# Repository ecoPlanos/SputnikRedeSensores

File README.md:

# SputnikRedeSensores

Open source project of a sensors test suit.

The goal is to develop a system to compare several sensors of each type out of several types.
The sensors will be assembled on a PCB for each type, that will connect to an Arduino Due compatible shield.
A program running on the Arduino, will log sensors data to a SD card and make it accessible through a FTP server.

types of sensors:
Temperature and relative humidity;
Superficial temperature;
Motion detection;
Air quality;
Electrical current;
Water flow;
Proximity;
Distance;
Microwave;
Lumen;
UV.

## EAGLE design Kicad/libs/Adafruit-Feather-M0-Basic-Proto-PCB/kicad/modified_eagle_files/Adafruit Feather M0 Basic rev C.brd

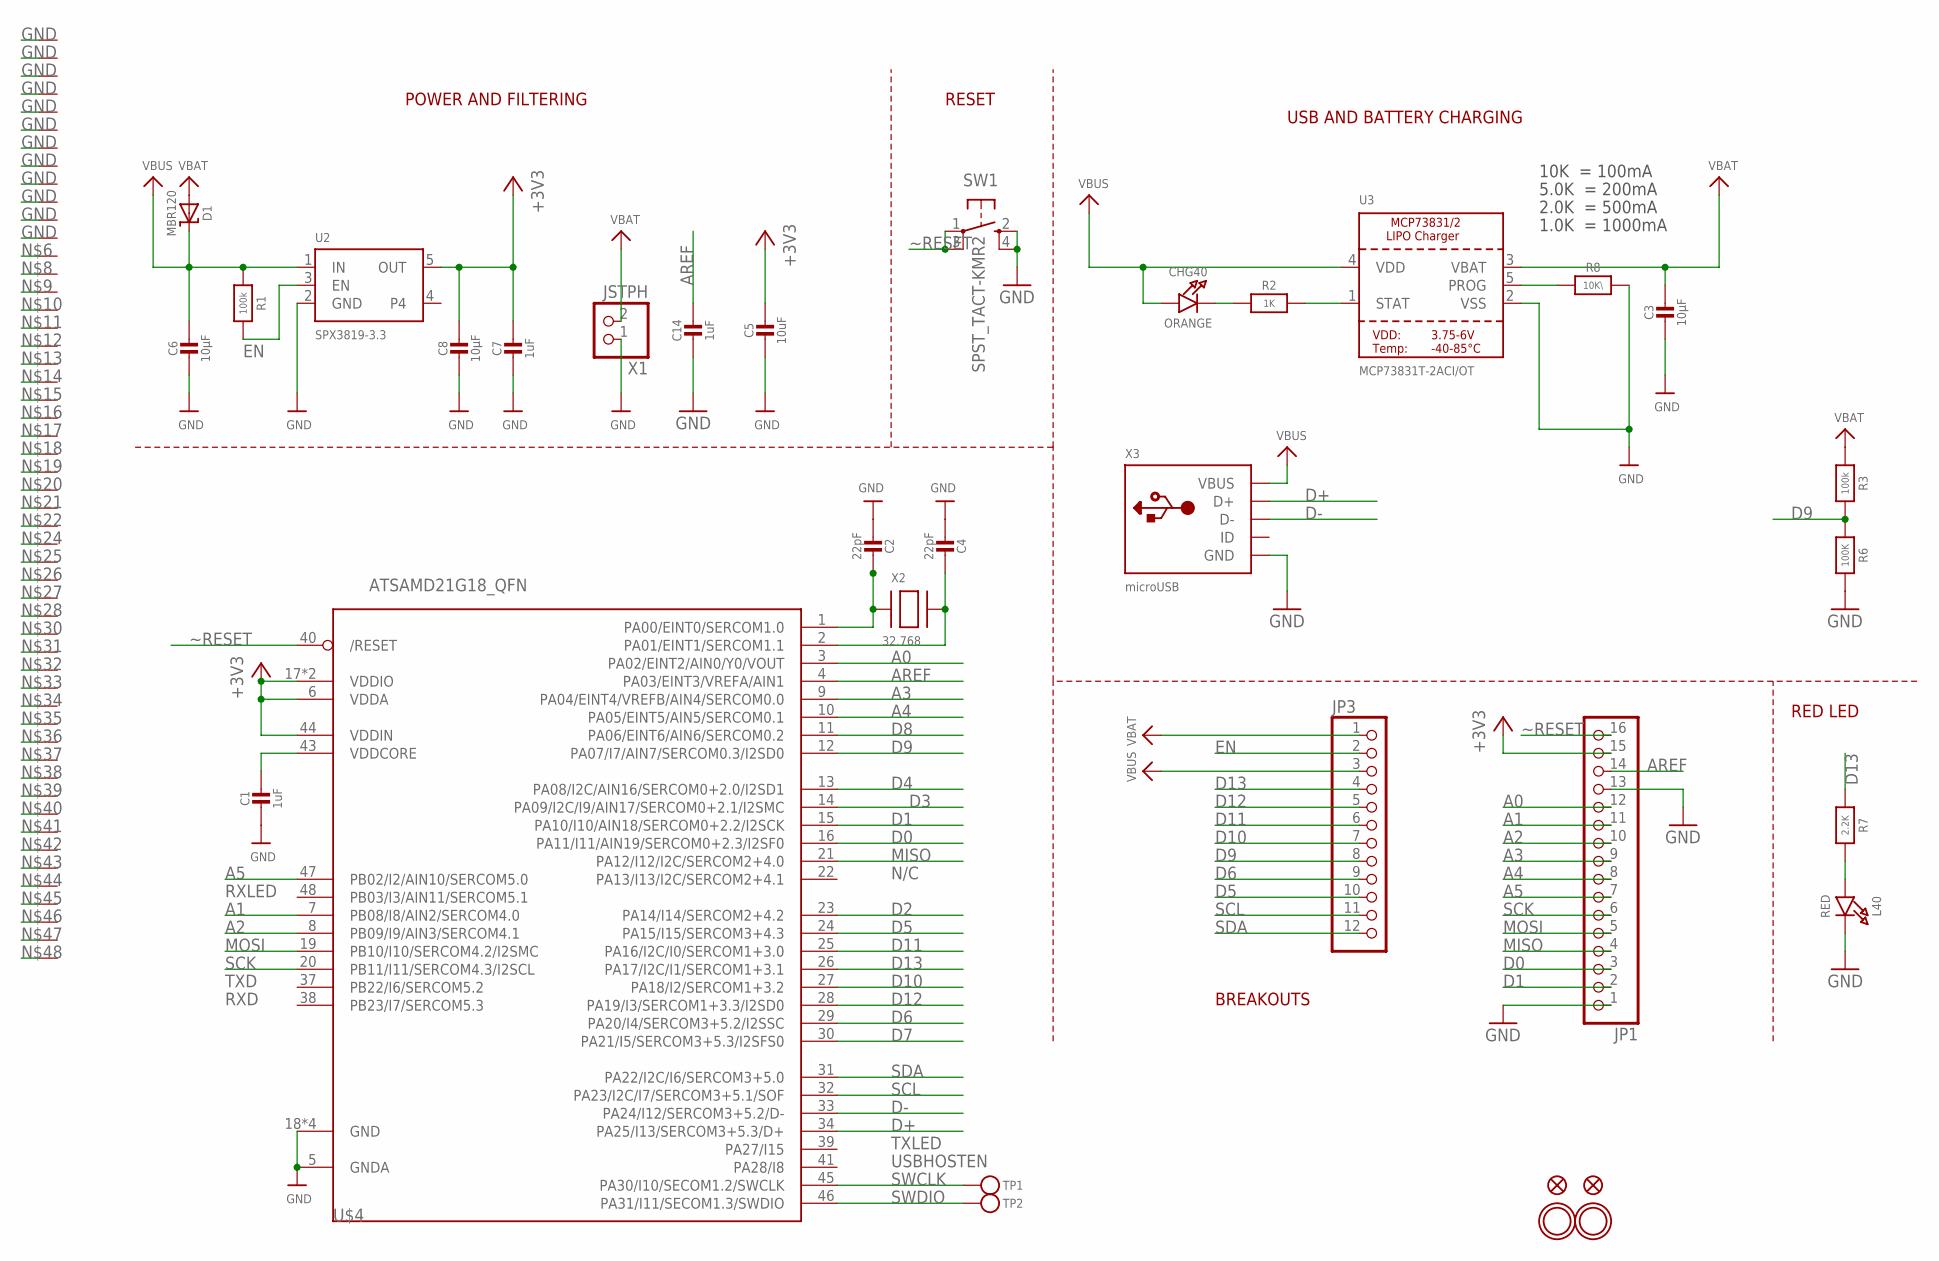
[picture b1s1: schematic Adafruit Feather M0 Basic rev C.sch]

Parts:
C1, C7, C14: 1uF; 0603-NO
C2, C4: 22pF; 0603-NO
C3, C6, C8: 10µF; 0805-NO
C5: 10uF; 0805-NO
CHG40: ORANGE; CHIPLED_0805_NOOUTLINE
D1: MBR120; SOD-123
JP1: HEADER-1X16ROUND; 1X16_ROUND
JP3: HEADER-1X12; 1X12_ROUND
L40: RED; CHIPLED_0805_NOOUTLINE
R1, R3: 100k; 0603-NO
R2: 1K; 0603-NO
R6: 100K; 0603-NO
R7: 2.2K; 0603-NO
R8: 10K\; 0603-NO
SW1: SPST_TACT-KMR2; KMR2
TP1, TP2: TESTPOINTROUND1.5MM; TESTPOINT_ROUND_1.5MM
U2: SPX3819-3.3; SOT23-5
U3: MCP73831T-2ACI/OT; SOT23-5
U$4: ATSAMD21G18_QFN; TQFN48_7MM
U$31, U$32: MOUNTINGHOLE2.5; MOUNTINGHOLE_2.5_PLATED
U$34, U$35: FIDUCIAL""; FIDUCIAL_1MM
VP_0, VP_1, VP_2, VP_3, VP_4, VP_5, VP_6, VP_7, VP_8, VP_9, VP_10, VP_11: VPDEV0; VPAC0
VP_12, VP_13, VP_14, VP_15, VP_16, VP_17, VP_18, VP_19, VP_20, VP_21, VP_22, VP_23, VP_24, VP_25, VP_26, VP_27, VP_28, VP_29, VP_30, VP_31, VP_32, VP_33, VP_34, VP_35, VP_36, VP_37, VP_38, VP_39, VP_40, VP_41, VP_42, VP_43, VP_44, VP_45, VP_46, VP_47, VP_48, VP_49, VP_50, VP_51: VPDEV1; VPAC1
X1: JSTPH; JSTPH2
X2: 32.768; XTAL3215
X3: microUSB; 4UCONN_20329_V2

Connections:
+3V3: C5.1, C7.1, C8.1, JP1.15, U2.5 (OUT), U$4.6 (VDDA), U$4.17 (VDDIO), U$4.36 (VDDIO), U$4.44 (VDDIN)
A0: JP1.12, U$4.3 (PA02/EINT2/AIN0/Y0/VOUT)
A1: JP1.11, U$4.7 (PB08/I8/AIN2/SERCOM4.0)
A2: JP1.10, U$4.8 (PB09/I9/AIN3/SERCOM4.1)
A3: JP1.9, U$4.9 (PA04/EINT4/VREFB/AIN4/SERCOM0.0)
A4: JP1.8, U$4.10 (PA05/EINT5/AIN5/SERCOM0.1)
A5: JP1.7, U$4.47 (PB02/I2/AIN10/SERCOM5.0)
AREF: C14.1, JP1.14, U$4.4 (PA03/EINT3/VREFA/AIN1)
D0: JP1.3, U$4.16 (PA11/I11/AIN19/SERCOM0+2.3/I2SF0)
D1: JP1.2, U$4.15 (PA10/I10/AIN18/SERCOM0+2.2/I2SCK)
D2: U$4.23 (PA14/I14/SERCOM2+4.2)
D3: U$4.14 (PA09/I2C/I9/AIN17/SERCOM0+2.1/I2SMC)
D4: U$4.13 (PA08/I2C/AIN16/SERCOM0+2.0/I2SD1)
D5: JP3.10, U$4.24 (PA15/I15/SERCOM3+4.3)
D6: JP3.9, U$4.29 (PA20/I4/SERCOM3+5.2/I2SSC)
D7: U$4.30 (PA21/I5/SERCOM3+5.3/I2SFS0)
D8: U$4.11 (PA06/EINT6/AIN6/SERCOM0.2)
D9: JP3.8, R3.2, R6.1, U$4.12 (PA07/I7/AIN7/SERCOM0.3/I2SD0)
D10: JP3.7, U$4.27 (PA18/I2/SERCOM1+3.2)
D11: JP3.6, U$4.25 (PA16/I2C/I0/SERCOM1+3.0)
D12: JP3.5, U$4.28 (PA19/I3/SERCOM1+3.3/I2SD0)
D13: JP3.4, R7.1, U$4.26 (PA17/I2C/I1/SERCOM1+3.1)
D+: U$4.34 (PA25/I13/SERCOM3+5.3/D+), X3.D+
D-: U$4.33 (PA24/I12/SERCOM3+5.2/D-), X3.D-
EN: JP3.2, R1.2, U2.3 (EN)
GND: C1.2, C2.2, C3.2, C4.2, C5.2, C6.2, C7.2, C8.2, C14.2, JP1.1, JP1.13, L40.C, R6.2, R8.2, SW1.2 (S), SW1.4 (S1), U2.2 (GND), U3.2 (VSS), U$4.5 (GNDA), U$4.18 (GND), U$4.35 (GND), U$4.42 (GND), U$4.THERMAL (GND), VP_0.VP, VP_1.VP, VP_2.VP, VP_3.VP, VP_4.VP, VP_5.VP, VP_6.VP, VP_7.VP, VP_8.VP, VP_9.VP, VP_10.VP, VP_11.VP, X1.1, X3.BASE@1 (GND), X3.BASE@2 (GND), X3.GND, X3.SPRT@1 (GND), X3.SPRT@2 (GND), X3.SPRT@3 (GND), X3.SPRT@4 (GND)
MISO: JP1.4, U$4.21 (PA12/I12/I2C/SERCOM2+4.0)
MOSI: JP1.5, U$4.19 (PB10/I10/SERCOM4.2/I2SMC)
unnamed: CHG40.C, R2.1
unnamed: L40.A, R7.2
unnamed: R2.2, U3.1 (STAT)
unnamed: R8.1, U3.5 (PROG)
unnamed: C2.1, U$4.1 (PA00/EINT0/SERCOM1.0), X2.P$1
unnamed: C4.1, U$4.2 (PA01/EINT1/SERCOM1.1), X2.P$2
SCK: JP1.6, U$4.20 (PB11/I11/SERCOM4.3/I2SCL)
SCL: JP3.11, U$4.32 (PA23/I2C/I7/SERCOM3+5.1/SOF)
SDA: JP3.12, U$4.31 (PA22/I2C/I6/SERCOM3+5.0)
SWCLK: TP1.P$1, U$4.45 (PA30/I10/SECOM1.2/SWCLK)
SWDIO: TP2.P$1, U$4.46 (PA31/I11/SECOM1.3/SWDIO)
VBAT: C3.1, D1.A, JP3.1, R3.1, U3.3 (VBAT), X1.2
VBUS: C6.1, CHG40.A, D1.C, JP3.3, R1.1, U2.1 (IN), U3.4 (VDD), X3.VBUS
VDDCORE: C1.1, U$4.43 (VDDCORE)
~RESET: JP1.16, SW1.1, SW1.3 (P1), U$4.40 (/RESET)

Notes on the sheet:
POWER AND FILTERING
RESET
10K = 100mA
5.0K = 200mA
2.0K = 500mA
1.0K = 1000mA
N/C
TXLED
USBHOSTEN
RXLED
TXD
RXD
USB AND BATTERY CHARGING
BREAKOUTS
RED LED

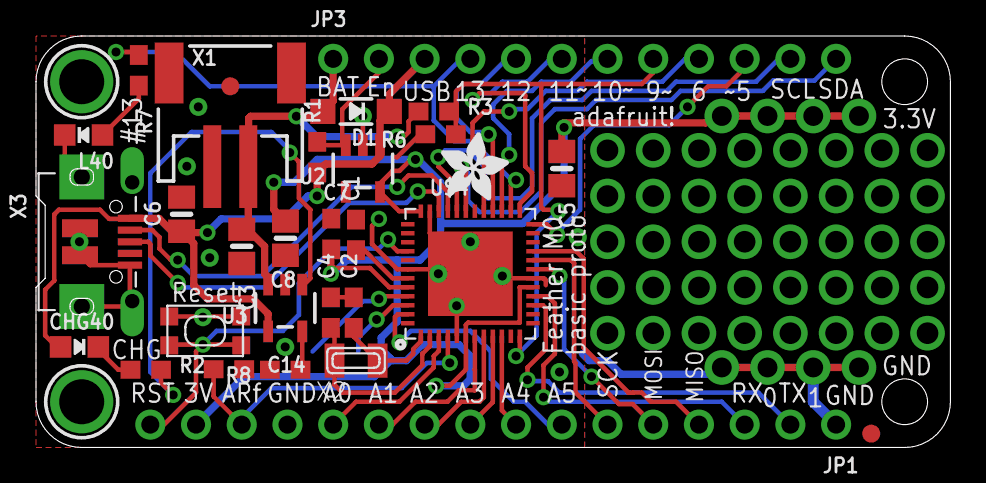
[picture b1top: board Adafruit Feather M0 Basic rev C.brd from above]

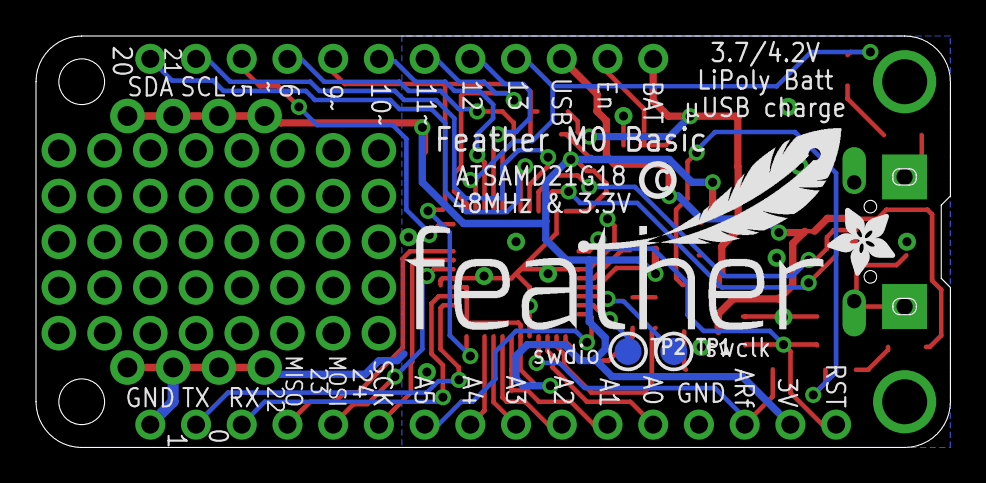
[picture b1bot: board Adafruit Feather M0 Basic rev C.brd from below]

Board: 2 copper layers, 50.8 x 22.9 mm, 89 parts (5 on the bottom side), 38 nets.

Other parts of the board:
U$7, U$12: ADAFRUIT_3.5MM
U$9: FEATHERLOGO
U$13: PCBFEAT-REV-040

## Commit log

2017-06-10 Hello world dos commit o comuna não sabe fazer pipocas
2017-06-10 adicao readme
2017-06-10 teste
2017-06-10 removido teste
2017-06-10 Removido teste do Rui
2017-06-10 Ao copiar o link do git, selecionar ssh
2017-06-10 Adicionados ficheiros de projeto do Platformio, com os arduinos que vão ser utilizados.
2017-06-10 Adicionadas bibliotecas para alguns dos senssores a utilizar. Adicionados ficheiros do projeto em PlatformIO ide.
2017-06-26 Atualizado main.cpp para implementar web server para log de dados. Adicionado comando de compilação do PlatformIO para arduino due
2017-06-28 Adicionadas algumas bibliotecas de sensores. @ST_HW_HC_SR04: Adicionadas funções para calculo de distância.
2017-06-30 Desenvolvido serial logger para sensores DHT11,DHT22 e SHT31.
2017-07-05 Added libs for MLX90614 and SHT75. Configured sht75 and MLX90614.
2017-07-05 Added data logging to SD card. Stable version (HR)!!!
2017-07-10 Added header to main.cpp Added libs for RTC and Wifi.
2017-07-11 Added Kicad project for temperature and relative humidity sensors test board.
2017-07-12 Finished Temperature and RH sensors! MLX temperature sensor is working. Made changes on libraries. Code refactoring.
2017-07-12 Finished Gas sensors implementation and testing. Designed PCB for Gas sensors.
2017-07-14 Added PCB project for T&RH sensors by AndreBotCardoso. Moved Gas sensor's PCB projec directory. Added Main_board PCB project.
2017-07-14 Edited README.md.
2017-07-16 Added air quality sensor to Kicad Gas schematic. Added code for CCS811. Note: arduino program is temporarily not compiling.
2017-07-16 Gas sensor CCS188 was missing and is now programed.
2017-07-17 Added RTC. RTC integration with SD file paths and log files. Added time tag to data log.
2017-07-25 Temperature and Temperature+RH (TTRH) sensors are all implemented. All sensors were tested, except Thermopar temperature sensor. Added TTRH shield schematic and layout (missing SDA1 and SCL1 for SHT7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
2017-07-25 Changes made on the file structure (not yet finished). Added Arduino project for Gas, Current, Motion, Reed and Distance sensors (GCMRD). Modifyed Temp_HR shield to add the MLX sensor.
2017-07-25 Added PT100 conditioning circuit to Tem_HR shield. Ready for testing!
2017-08-08 Revision v1.0! @Arduino/Temp_HR: - Added implentation of thermopar sensor - Added sensors error check routines and recovery Finished file structure changes.Revision v1.0! @Arduino/Temp_HR: - Added im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
2017-08-08 Added Arduino and Kicad projects for Arduino Pro Mini 328. SHT31 is working on the Pro Mini.
2017-08-16 Arduino Pro mini implementation is finished! Arduino Due is only missing a conversion of the input characters from remote station to the CSV format adopted for storage.
2017-08-19 Arduino Release 2.00! Finished implementation of final setup with arduino due and pro mini.
2017-08-21 Resolved ntc bug; Added resistance calculation for NTC; Fixed config file; Added readme.txt auto-write to SD card.
2017-08-22 correcção de caminho no projecto kicad do Gas
2017-08-23 Corrected kicad paths for gas sensors module
2017-08-23 Corrected kicad libraries. Added ecoPlanos libs.
2017-08-23 Added PH4 connectors libs; Finshed CO2 sensors schematic circuit.
2017-08-23 Changed organization of kicad current and gas projects.
2017-08-23 Created Kicad project for the Sink Module
2017-08-23 @Kicad/Gas_Current_Sink/Gas: Finished PCB edge cutting and sensors placement project.
2017-08-24 ecoPlanos 20mm width logo added
2017-08-24 Gas sensors PCB V1.00a
2017-10-03 Store file header on log files; Reset Arduino @ midnight to avoid large data files; Changed loged timestamp to date/time.
2017-10-03 Updated readme file; Fixed loop delay bug.
2017-10-10 dimensionamento cs
2017-10-11 Kicad Current project update Kicad TH project update
2017-10-14 Revision V2.0! New version of remote aquisition system for Temperature and humidity.
2017-10-18 Update to schematic and pcb almost complete (drill holes missing)
2017-10-19 @Gas_Current module - added kicad project for arduino due.
2017-10-19 Minor changes on pcb routing.
2017-10-29 Changed Gas Current kicad directory structure.
2017-10-29 Added some lables to schematic.
2017-11-10 small changes on tem&rh arduino code.
2017-11-10 Current and CO2 Arduino and Kicad Release 1.00! Added Arduino code for CO2 and Current sensor module. Updated Kicad projects for Arduino Due shield and top of the box CO2 PCB.
2017-11-10 Small kicad update.
2017-11-10 Added Kicad projects for XBee module. Added Arduino project for feather M0 board used in the Light and Motion sensor modules.
2017-11-13 CO2 & Current Arduino final release with necessary calibrations. Minor file structure changes.
2017-11-13 Updated gitignore to exclude backup files
2017-11-16 Added XBee breakout board; Added Kicad project for motion sensors; Added script to convert eagle files to kicad; Added feather M0 library converted from eagle to Kicad. Deleted obsolete files.
2017-11-16 Corrected 3V3 bug!
2017-11-17 Updated Kicad Motion detection circuit and board. Updated Feather code to comunicate using XBee.
2017-11-17 Added missing libraries.
2017-11-18 Two new signal conditioning stages were added and the final pcb layout completed.
2017-11-18 @ Motion detection Arduino project - Release 1.00 @ Gas Current Arduino project - added Serial interface to get data from XBee connected Motion sensors.
2017-11-19 Status led pin added to schematic and PCB.
2017-11-20 Added Arduino project for Light sensors module. Changed Gas Current Arduino project to comunicate with the other modules.
2017-11-20 Added light sensors Kicad shield project
2017-11-21 @Arduino/Light .Corrected delay_ms initialization .Added compatibility with feather and arduino pro mini.
2017-11-24 @Arduino - minor bug corrections.
2017-11-29 Schematic and PCB of Reed, Movment and Distance sensors module
2017-11-30 Corrected distance sensors bug. Added jumper to enable or disable Xbee, to access arduino pro mini serial port.
2017-11-30 Corrected SDA and SCL switched bug.
2017-12-04 Added arduino project for distance, accelerometer, gyroscope and reed sensors to monitor windows and blinds motion.
2017-12-05 Changed Gas/Current Arduino project to log different sensor data to different files.
2017-12-05 Gas_Current Arduino bugs correction.
2017-12-06 @Arduino Gas_Current, implemented configuration for multiple sensor modules sampling frequency
2017-12-06 @Arduino Gas_Current project: final bug corrections.

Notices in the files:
parts and their libraries:
microbuilder: This work is placed in the public domain, and may be freely used for commercial and non-commercial work with the following conditions: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
